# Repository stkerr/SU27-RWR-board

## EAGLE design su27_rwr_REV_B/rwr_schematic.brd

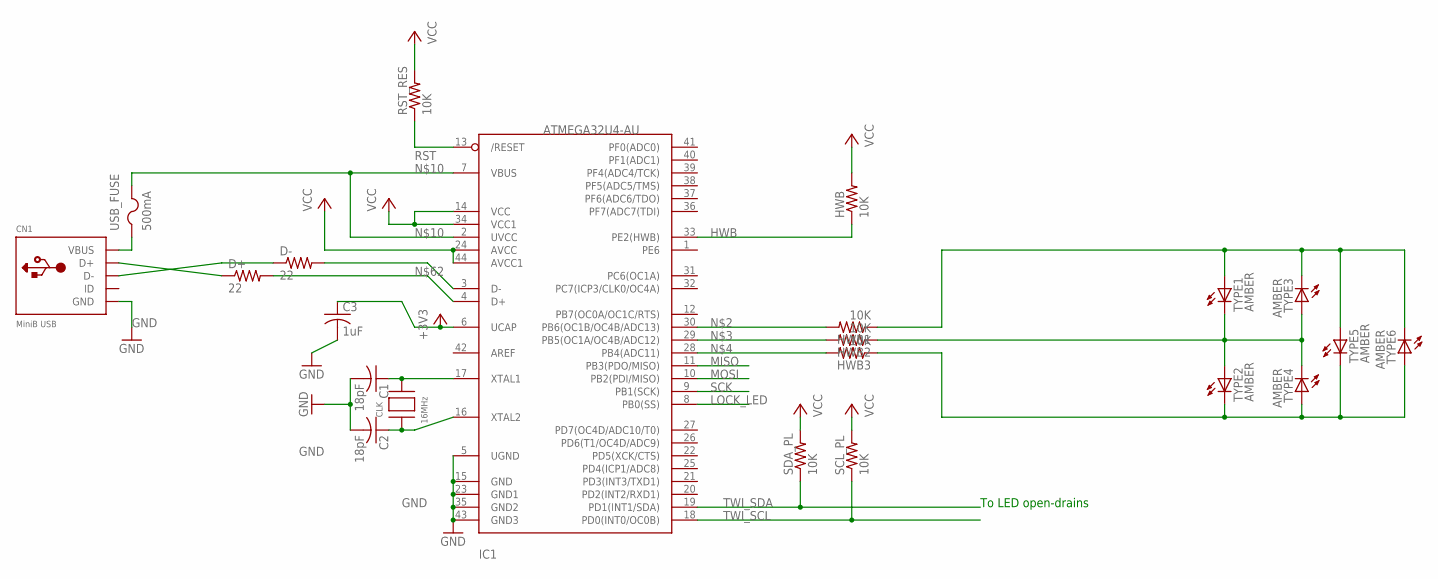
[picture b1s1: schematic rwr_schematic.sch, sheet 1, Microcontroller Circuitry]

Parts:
C1, C2: 18pF; C0805K
C3: 1uF; C0805K
CLK: 16MHz; NX5032
CN1: MiniB USB; USB-MINIB
D+: 22; R0805
D-: 22; R0805
HWB, HWB1, HWB2, HWB3: 10K; R0805
IC1: ATMEGA32U4-AU; TQFP44
RST_RES: 10K; R0805
SCL_PL: 10K; R0805
SDA_PL: 10K; R0805
TYPE1, TYPE2, TYPE3, TYPE4, TYPE5, TYPE6: AMBER; LED3MM
USB_FUSE: 500mA; R1206

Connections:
+3V3: C3.1, IC1.6 (UCAP)
GND: C1.2, C2.2, C3.2, CN1.GND, IC1.5 (UGND), IC1.15 (GND), IC1.23 (GND1), IC1.35 (GND2), IC1.43 (GND3); also elsewhere on the board
HWB: HWB.1, IC1.33 (PE2(HWB))
LOCK_LED: IC1.8 (PB0(SS)); also elsewhere on the board
MISO: IC1.11 (PB3(PDO/MISO)); also elsewhere on the board
MOSI: IC1.10 (PB2(PDI/MISO)); also elsewhere on the board
unnamed: HWB1.2, IC1.30 (PB6(OC1B/OC4B/ADC13))
unnamed: HWB2.2, IC1.29 (PB5(OC1A/OC4B/ADC12))
unnamed: HWB3.2, IC1.28 (PB4(ADC11))
unnamed: IC1.2 (UVCC), IC1.7 (VBUS), USB_FUSE.2
unnamed: D-.2, IC1.3 (D-)
unnamed: D+.2, IC1.4 (D+)
unnamed: C2.1, CLK.P$1, IC1.16 (XTAL2)
unnamed: C1.1, CLK.P$2, IC1.17 (XTAL1)
unnamed: CN1.D+, D+.1
unnamed: CN1.D-, D-.1
RST: IC1.13 (/RESET), RST_RES.1; also elsewhere on the board
SCK: IC1.9 (PB1(SCK)); also elsewhere on the board
TWI_SCL: IC1.18 (PD0(INT0/OC0B)), SCL_PL.1; also elsewhere on the board
TWI_SDA: IC1.19 (PD1(INT1/SDA)), SDA_PL.1; also elsewhere on the board
TYPE_LED0: HWB3.1, TYPE2.K (C), TYPE4.A, TYPE5.K (C), TYPE6.A
TYPE_LED1: HWB2.1, TYPE1.K (C), TYPE2.A, TYPE3.A, TYPE4.K (C)
TYPE_LED2: HWB1.1, TYPE1.A, TYPE3.K (C), TYPE5.A, TYPE6.K (C)
VBUS: CN1.VBUS, USB_FUSE.1
VCC: HWB.2, IC1.14 (VCC), IC1.24 (AVCC), IC1.34 (VCC1), IC1.44 (AVCC1), RST_RES.2, SCL_PL.2, SDA_PL.2; also elsewhere on the board

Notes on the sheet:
To LED open-drains

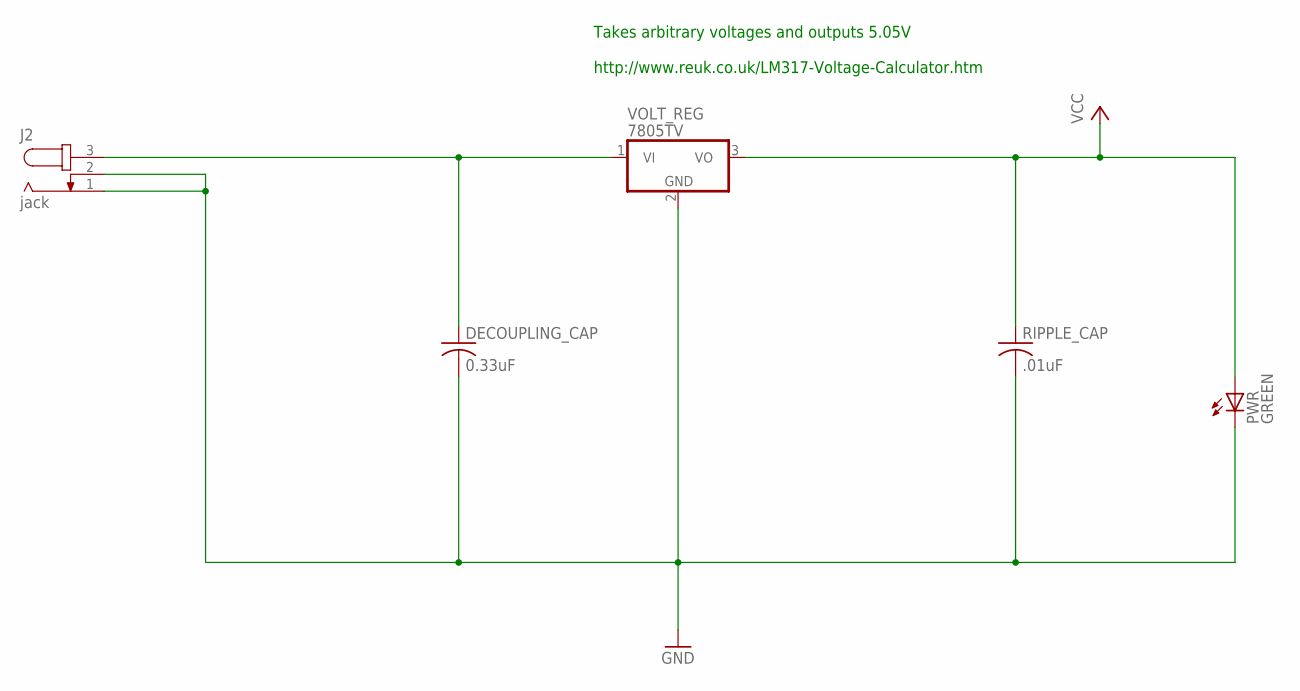
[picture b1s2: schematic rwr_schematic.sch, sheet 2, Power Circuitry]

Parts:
DECOUPLING_CAP: 0.33uF; C0805K
J2: jack; SPC4077
PWR: GREEN; CHIPLED_0805
RIPPLE_CAP: .01uF; C0805K
VOLT_REG: 7805TV; TO220V

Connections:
GND: DECOUPLING_CAP.2, J2.1, J2.2, PWR.C, RIPPLE_CAP.2, VOLT_REG.2 (GND); also elsewhere on the board
JACK_VCC: DECOUPLING_CAP.1, J2.3, VOLT_REG.1 (VI)
VCC: PWR.A, RIPPLE_CAP.1, VOLT_REG.3 (VO); also elsewhere on the board

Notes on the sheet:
Takes arbitrary voltages and outputs 5.05V http://www.reuk.co.uk/LM317-Voltage-Calculator.htm

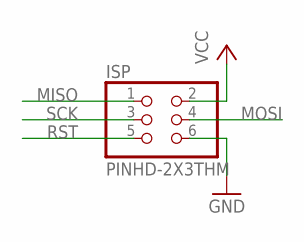
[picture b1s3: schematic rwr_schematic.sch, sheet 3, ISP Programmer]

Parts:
ISP: PINHD-2X3THM; ISP6

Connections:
GND: ISP.6; also elsewhere on the board
MISO: ISP.1; also elsewhere on the board
MOSI: ISP.4; also elsewhere on the board
RST: ISP.5; also elsewhere on the board
SCK: ISP.3; also elsewhere on the board
VCC: ISP.2; also elsewhere on the board

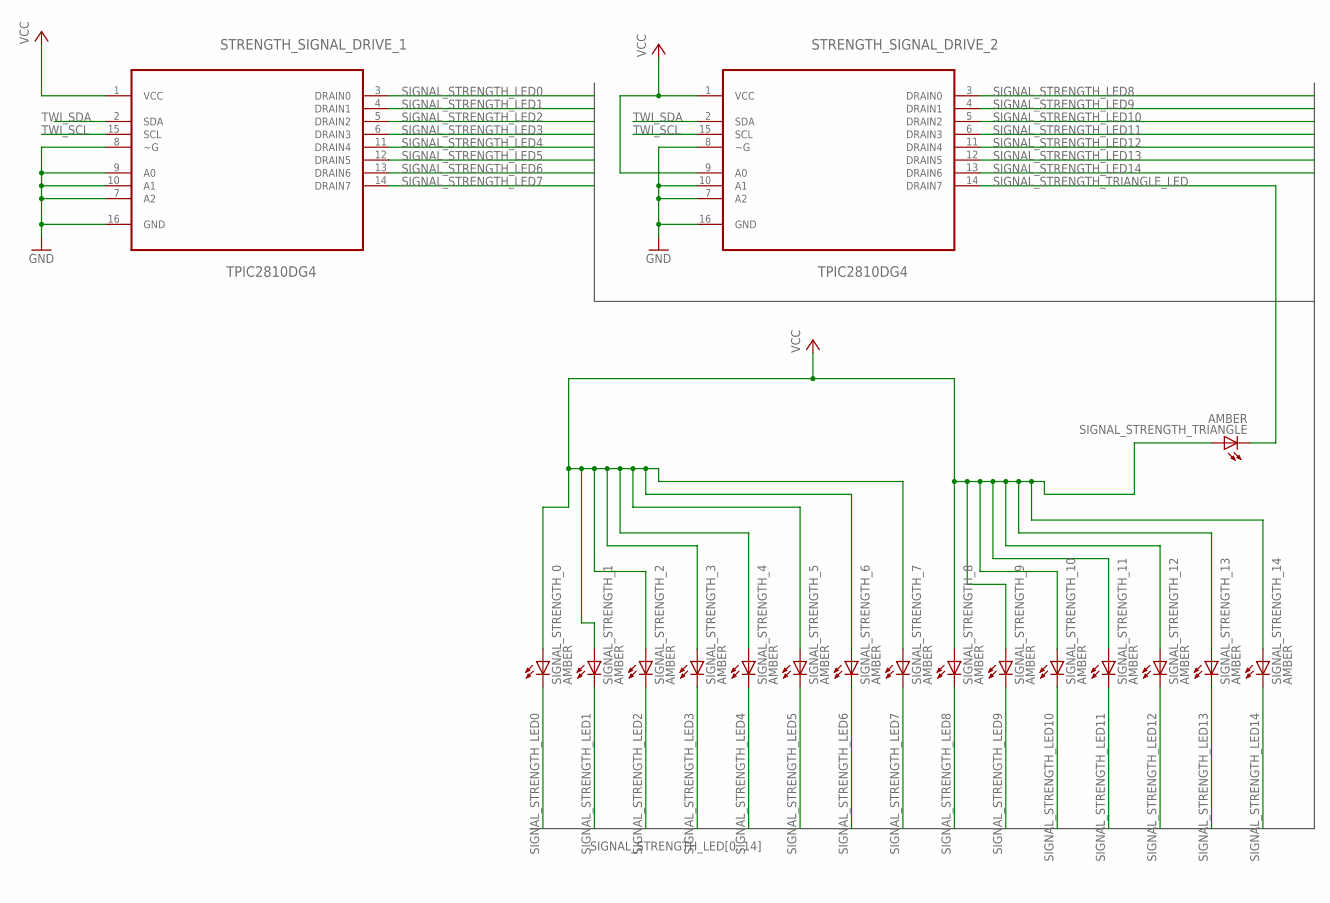
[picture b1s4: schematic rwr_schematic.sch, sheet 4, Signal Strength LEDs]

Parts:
SIGNAL_STRENGTH_0, SIGNAL_STRENGTH_1, SIGNAL_STRENGTH_2, SIGNAL_STRENGTH_3, SIGNAL_STRENGTH_4, SIGNAL_STRENGTH_5, SIGNAL_STRENGTH_6, SIGNAL_STRENGTH_7, SIGNAL_STRENGTH_8, SIGNAL_STRENGTH_9, SIGNAL_STRENGTH_10, SIGNAL_STRENGTH_11, SIGNAL_STRENGTH_12, SIGNAL_STRENGTH_13, SIGNAL_STRENGTH_14: AMBER; LED3MM
SIGNAL_STRENGTH_TRIANGLE: AMBER; LED3MM
STRENGTH_SIGNAL_DRIVE_1, STRENGTH_SIGNAL_DRIVE_2: TPIC2810DG4; SOIC127P600X175-16N

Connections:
GND: STRENGTH_SIGNAL_DRIVE_1.7 (A2), STRENGTH_SIGNAL_DRIVE_1.8 (~G), STRENGTH_SIGNAL_DRIVE_1.9 (A0), STRENGTH_SIGNAL_DRIVE_1.10 (A1), STRENGTH_SIGNAL_DRIVE_1.16 (GND), STRENGTH_SIGNAL_DRIVE_2.7 (A2), STRENGTH_SIGNAL_DRIVE_2.8 (~G), STRENGTH_SIGNAL_DRIVE_2.10 (A1), STRENGTH_SIGNAL_DRIVE_2.16 (GND); also elsewhere on the board
SIGNAL_STRENGTH_LED0: SIGNAL_STRENGTH_0.K (C), STRENGTH_SIGNAL_DRIVE_1.3 (DRAIN0)
SIGNAL_STRENGTH_LED1: SIGNAL_STRENGTH_1.K (C), STRENGTH_SIGNAL_DRIVE_1.4 (DRAIN1)
SIGNAL_STRENGTH_LED2: SIGNAL_STRENGTH_2.K (C), STRENGTH_SIGNAL_DRIVE_1.5 (DRAIN2)
SIGNAL_STRENGTH_LED3: SIGNAL_STRENGTH_3.K (C), STRENGTH_SIGNAL_DRIVE_1.6 (DRAIN3)
SIGNAL_STRENGTH_LED4: SIGNAL_STRENGTH_4.K (C), STRENGTH_SIGNAL_DRIVE_1.11 (DRAIN4)
SIGNAL_STRENGTH_LED5: SIGNAL_STRENGTH_5.K (C), STRENGTH_SIGNAL_DRIVE_1.12 (DRAIN5)
SIGNAL_STRENGTH_LED6: SIGNAL_STRENGTH_6.K (C), STRENGTH_SIGNAL_DRIVE_1.13 (DRAIN6)
SIGNAL_STRENGTH_LED7: SIGNAL_STRENGTH_7.K (C), STRENGTH_SIGNAL_DRIVE_1.14 (DRAIN7)
SIGNAL_STRENGTH_LED8: SIGNAL_STRENGTH_8.K (C), STRENGTH_SIGNAL_DRIVE_2.3 (DRAIN0)
SIGNAL_STRENGTH_LED9: SIGNAL_STRENGTH_9.K (C), STRENGTH_SIGNAL_DRIVE_2.4 (DRAIN1)
SIGNAL_STRENGTH_LED10: SIGNAL_STRENGTH_10.K (C), STRENGTH_SIGNAL_DRIVE_2.5 (DRAIN2)
SIGNAL_STRENGTH_LED11: SIGNAL_STRENGTH_11.K (C), STRENGTH_SIGNAL_DRIVE_2.6 (DRAIN3)
SIGNAL_STRENGTH_LED12: SIGNAL_STRENGTH_12.K (C), STRENGTH_SIGNAL_DRIVE_2.11 (DRAIN4)
SIGNAL_STRENGTH_LED13: SIGNAL_STRENGTH_13.K (C), STRENGTH_SIGNAL_DRIVE_2.12 (DRAIN5)
SIGNAL_STRENGTH_LED14: SIGNAL_STRENGTH_14.K (C), STRENGTH_SIGNAL_DRIVE_2.13 (DRAIN6)
SIGNAL_STRENGTH_TRIANGLE_LED: SIGNAL_STRENGTH_TRIANGLE.K (C), STRENGTH_SIGNAL_DRIVE_2.14 (DRAIN7)
TWI_SCL: STRENGTH_SIGNAL_DRIVE_1.15 (SCL), STRENGTH_SIGNAL_DRIVE_2.15 (SCL); also elsewhere on the board
TWI_SDA: STRENGTH_SIGNAL_DRIVE_1.2 (SDA), STRENGTH_SIGNAL_DRIVE_2.2 (SDA); also elsewhere on the board
VCC: SIGNAL_STRENGTH_0.A, SIGNAL_STRENGTH_1.A, SIGNAL_STRENGTH_2.A, SIGNAL_STRENGTH_3.A, SIGNAL_STRENGTH_4.A, SIGNAL_STRENGTH_5.A, SIGNAL_STRENGTH_6.A, SIGNAL_STRENGTH_7.A, SIGNAL_STRENGTH_8.A, SIGNAL_STRENGTH_9.A, SIGNAL_STRENGTH_10.A, SIGNAL_STRENGTH_11.A, SIGNAL_STRENGTH_12.A, SIGNAL_STRENGTH_13.A, SIGNAL_STRENGTH_14.A, SIGNAL_STRENGTH_TRIANGLE.A, STRENGTH_SIGNAL_DRIVE_1.1 (VCC), STRENGTH_SIGNAL_DRIVE_2.1 (VCC), STRENGTH_SIGNAL_DRIVE_2.9 (A0); also elsewhere on the board

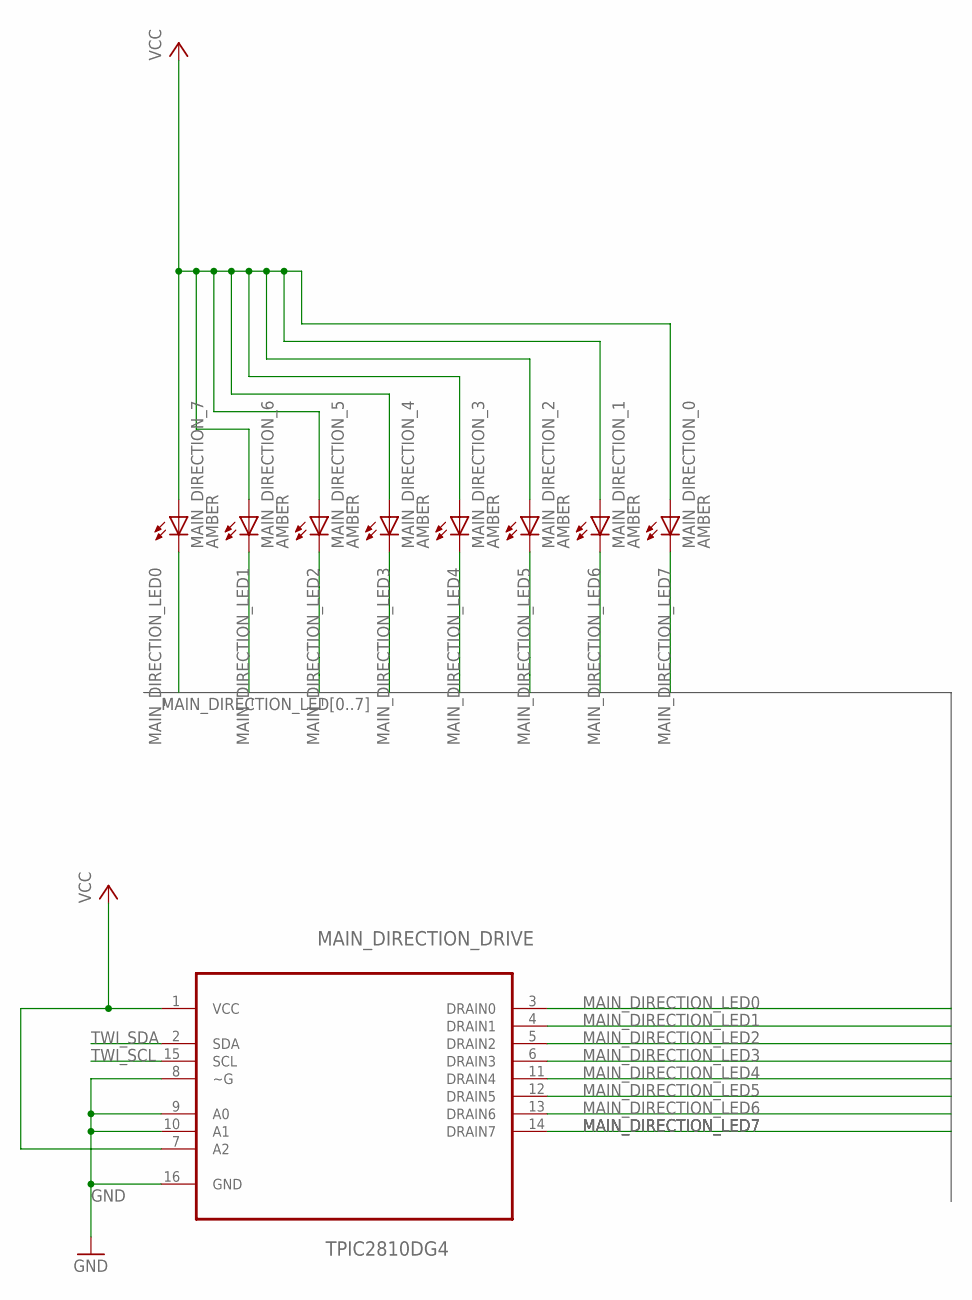
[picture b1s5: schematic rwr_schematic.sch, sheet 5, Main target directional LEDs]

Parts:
MAIN_DIRECTION_0, MAIN_DIRECTION_1, MAIN_DIRECTION_2, MAIN_DIRECTION_3, MAIN_DIRECTION_4, MAIN_DIRECTION_5, MAIN_DIRECTION_6, MAIN_DIRECTION_7: AMBER; LED3MM
MAIN_DIRECTION_DRIVE: TPIC2810DG4; SOIC127P600X175-16N

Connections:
GND: MAIN_DIRECTION_DRIVE.8 (~G), MAIN_DIRECTION_DRIVE.9 (A0), MAIN_DIRECTION_DRIVE.10 (A1), MAIN_DIRECTION_DRIVE.16 (GND); also elsewhere on the board
MAIN_DIRECTION_LED0: MAIN_DIRECTION_7.K (C), MAIN_DIRECTION_DRIVE.3 (DRAIN0)
MAIN_DIRECTION_LED1: MAIN_DIRECTION_6.K (C), MAIN_DIRECTION_DRIVE.4 (DRAIN1)
MAIN_DIRECTION_LED2: MAIN_DIRECTION_5.K (C), MAIN_DIRECTION_DRIVE.5 (DRAIN2)
MAIN_DIRECTION_LED3: MAIN_DIRECTION_4.K (C), MAIN_DIRECTION_DRIVE.6 (DRAIN3)
MAIN_DIRECTION_LED4: MAIN_DIRECTION_3.K (C), MAIN_DIRECTION_DRIVE.11 (DRAIN4)
MAIN_DIRECTION_LED5: MAIN_DIRECTION_2.K (C), MAIN_DIRECTION_DRIVE.12 (DRAIN5)
MAIN_DIRECTION_LED6: MAIN_DIRECTION_1.K (C), MAIN_DIRECTION_DRIVE.13 (DRAIN6)
MAIN_DIRECTION_LED7: MAIN_DIRECTION_0.K (C), MAIN_DIRECTION_DRIVE.14 (DRAIN7)
TWI_SCL: MAIN_DIRECTION_DRIVE.15 (SCL); also elsewhere on the board
TWI_SDA: MAIN_DIRECTION_DRIVE.2 (SDA); also elsewhere on the board
VCC: MAIN_DIRECTION_0.A, MAIN_DIRECTION_1.A, MAIN_DIRECTION_2.A, MAIN_DIRECTION_3.A, MAIN_DIRECTION_4.A, MAIN_DIRECTION_5.A, MAIN_DIRECTION_6.A, MAIN_DIRECTION_7.A, MAIN_DIRECTION_DRIVE.1 (VCC), MAIN_DIRECTION_DRIVE.7 (A2); also elsewhere on the board

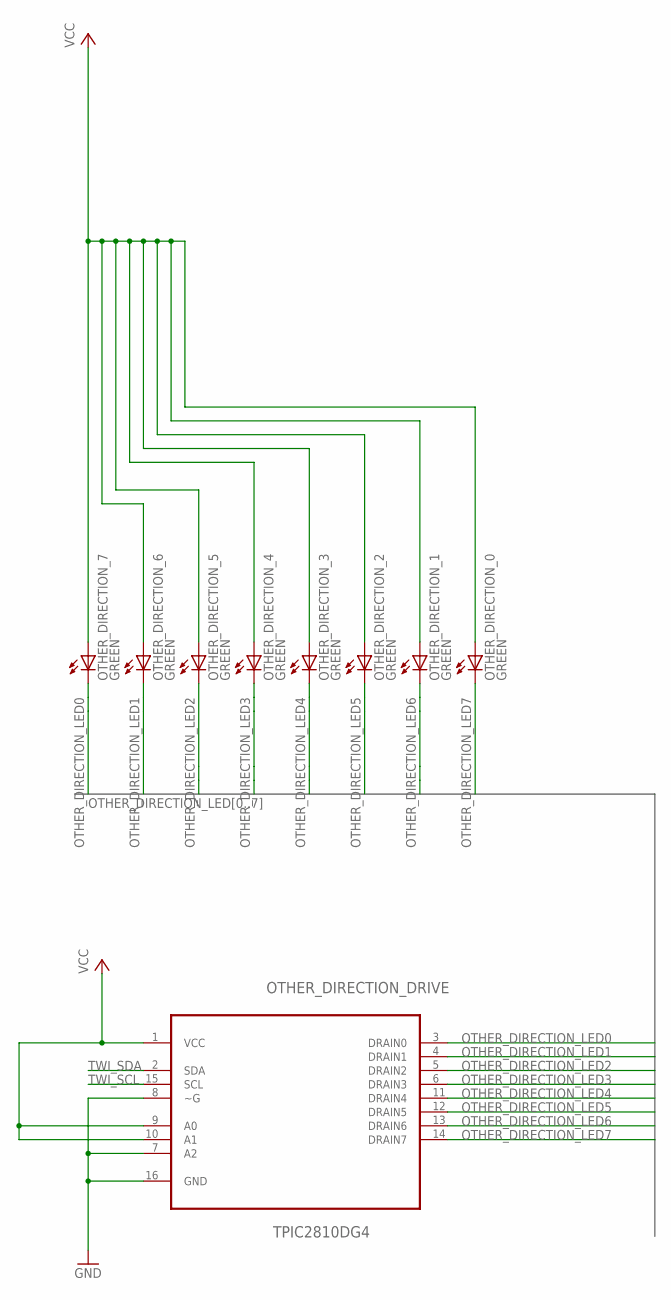
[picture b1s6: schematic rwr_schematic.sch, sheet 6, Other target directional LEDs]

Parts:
OTHER_DIRECTION_0, OTHER_DIRECTION_1, OTHER_DIRECTION_2, OTHER_DIRECTION_3, OTHER_DIRECTION_4, OTHER_DIRECTION_5, OTHER_DIRECTION_6, OTHER_DIRECTION_7: GREEN; LED3MM
OTHER_DIRECTION_DRIVE: TPIC2810DG4; SOIC127P600X175-16N

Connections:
GND: OTHER_DIRECTION_DRIVE.7 (A2), OTHER_DIRECTION_DRIVE.8 (~G), OTHER_DIRECTION_DRIVE.16 (GND); also elsewhere on the board
OTHER_DIRECTION_LED0: OTHER_DIRECTION_7.K (C), OTHER_DIRECTION_DRIVE.3 (DRAIN0)
OTHER_DIRECTION_LED1: OTHER_DIRECTION_6.K (C), OTHER_DIRECTION_DRIVE.4 (DRAIN1)
OTHER_DIRECTION_LED2: OTHER_DIRECTION_5.K (C), OTHER_DIRECTION_DRIVE.5 (DRAIN2)
OTHER_DIRECTION_LED3: OTHER_DIRECTION_4.K (C), OTHER_DIRECTION_DRIVE.6 (DRAIN3)
OTHER_DIRECTION_LED4: OTHER_DIRECTION_3.K (C), OTHER_DIRECTION_DRIVE.11 (DRAIN4)
OTHER_DIRECTION_LED5: OTHER_DIRECTION_2.K (C), OTHER_DIRECTION_DRIVE.12 (DRAIN5)
OTHER_DIRECTION_LED6: OTHER_DIRECTION_1.K (C), OTHER_DIRECTION_DRIVE.13 (DRAIN6)
OTHER_DIRECTION_LED7: OTHER_DIRECTION_0.K (C), OTHER_DIRECTION_DRIVE.14 (DRAIN7)
TWI_SCL: OTHER_DIRECTION_DRIVE.15 (SCL); also elsewhere on the board
TWI_SDA: OTHER_DIRECTION_DRIVE.2 (SDA); also elsewhere on the board
VCC: OTHER_DIRECTION_0.A, OTHER_DIRECTION_1.A, OTHER_DIRECTION_2.A, OTHER_DIRECTION_3.A, OTHER_DIRECTION_4.A, OTHER_DIRECTION_5.A, OTHER_DIRECTION_6.A, OTHER_DIRECTION_7.A, OTHER_DIRECTION_DRIVE.1 (VCC), OTHER_DIRECTION_DRIVE.9 (A0), OTHER_DIRECTION_DRIVE.10 (A1); also elsewhere on the board

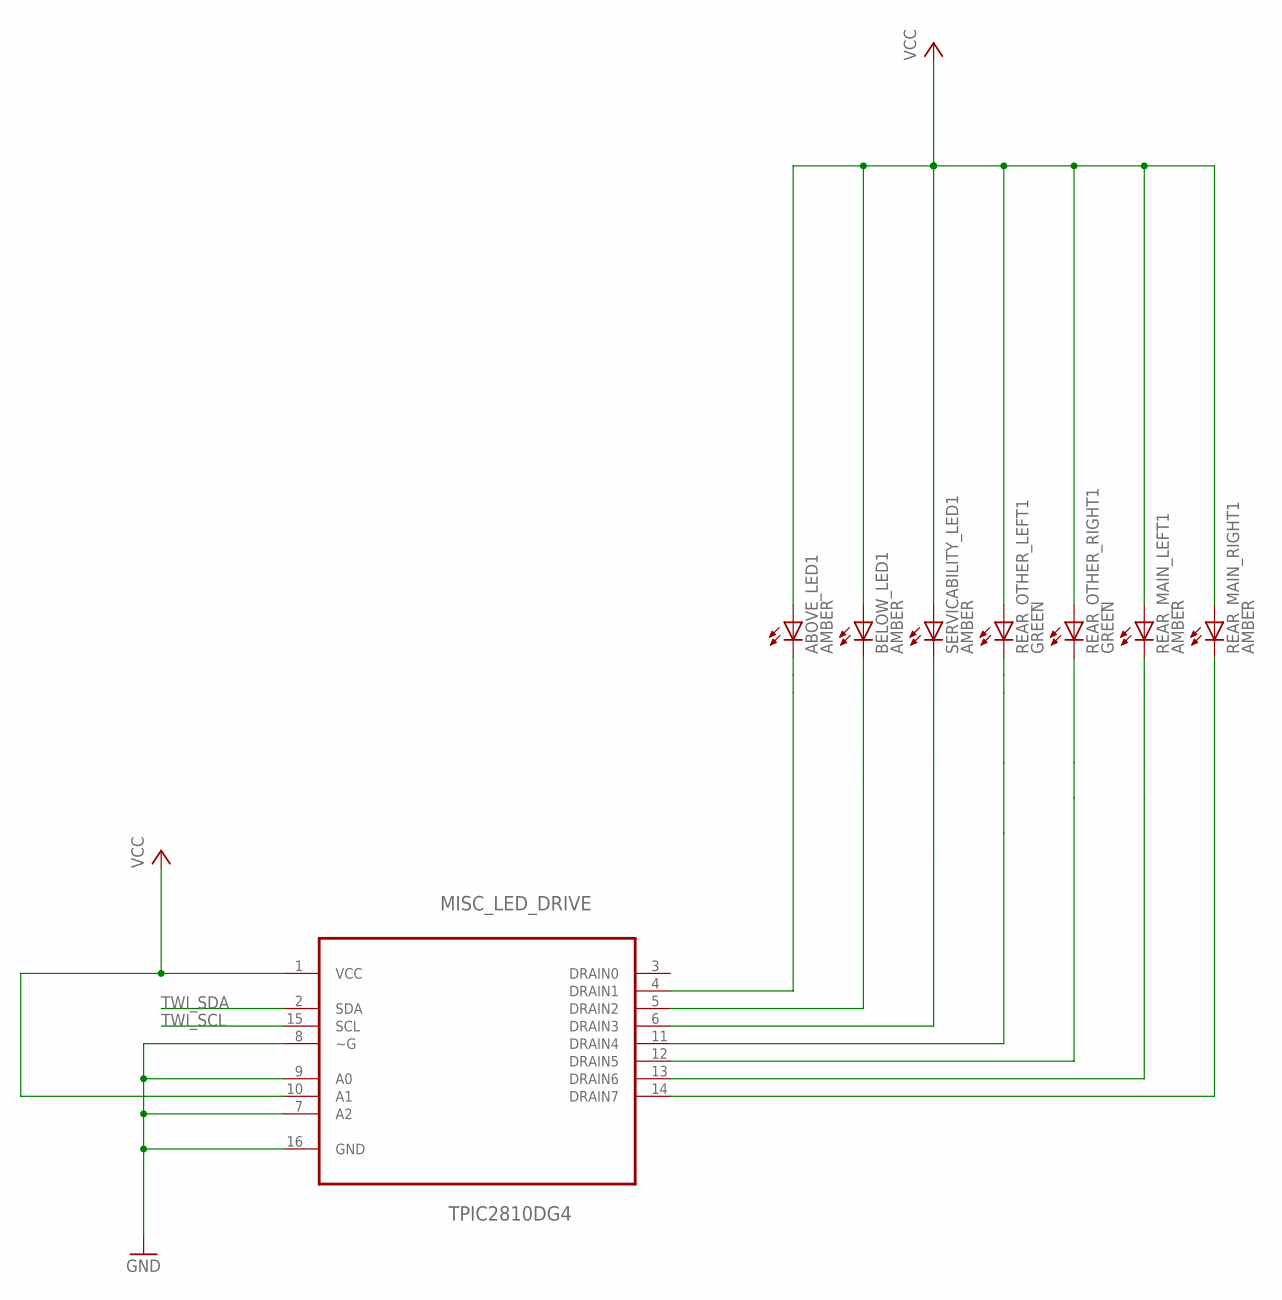
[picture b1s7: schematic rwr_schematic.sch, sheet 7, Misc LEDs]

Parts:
ABOVE_LED1: AMBER; LED3MM
BELOW_LED1: AMBER; LED3MM
MISC_LED_DRIVE: TPIC2810DG4; SOIC127P600X175-16N
REAR_MAIN_LEFT1: AMBER; LED3MM
REAR_MAIN_RIGHT1: AMBER; LED3MM
REAR_OTHER_LEFT1: GREEN; LED3MM
REAR_OTHER_RIGHT1: GREEN; LED3MM
SERVICABILITY_LED1: AMBER; LED3MM

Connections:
GND: MISC_LED_DRIVE.7 (A2), MISC_LED_DRIVE.8 (~G), MISC_LED_DRIVE.9 (A0), MISC_LED_DRIVE.16 (GND); also elsewhere on the board
unnamed: MISC_LED_DRIVE.12 (DRAIN5), REAR_OTHER_RIGHT1.K (C)
unnamed: MISC_LED_DRIVE.14 (DRAIN7), REAR_MAIN_RIGHT1.K (C)
unnamed: ABOVE_LED1.K (C), MISC_LED_DRIVE.4 (DRAIN1)
unnamed: MISC_LED_DRIVE.6 (DRAIN3), SERVICABILITY_LED1.K (C)
unnamed: MISC_LED_DRIVE.11 (DRAIN4), REAR_OTHER_LEFT1.K (C)
unnamed: BELOW_LED1.K (C), MISC_LED_DRIVE.5 (DRAIN2)
REAR_MAIN_LEFT1: MISC_LED_DRIVE.13 (DRAIN6), REAR_MAIN_LEFT1.K (C)
TWI_SCL: MISC_LED_DRIVE.15 (SCL); also elsewhere on the board
TWI_SDA: MISC_LED_DRIVE.2 (SDA); also elsewhere on the board
VCC: ABOVE_LED1.A, BELOW_LED1.A, MISC_LED_DRIVE.1 (VCC), MISC_LED_DRIVE.10 (A1), REAR_MAIN_LEFT1.A, REAR_MAIN_RIGHT1.A, REAR_OTHER_LEFT1.A, REAR_OTHER_RIGHT1.A, SERVICABILITY_LED1.A; also elsewhere on the board

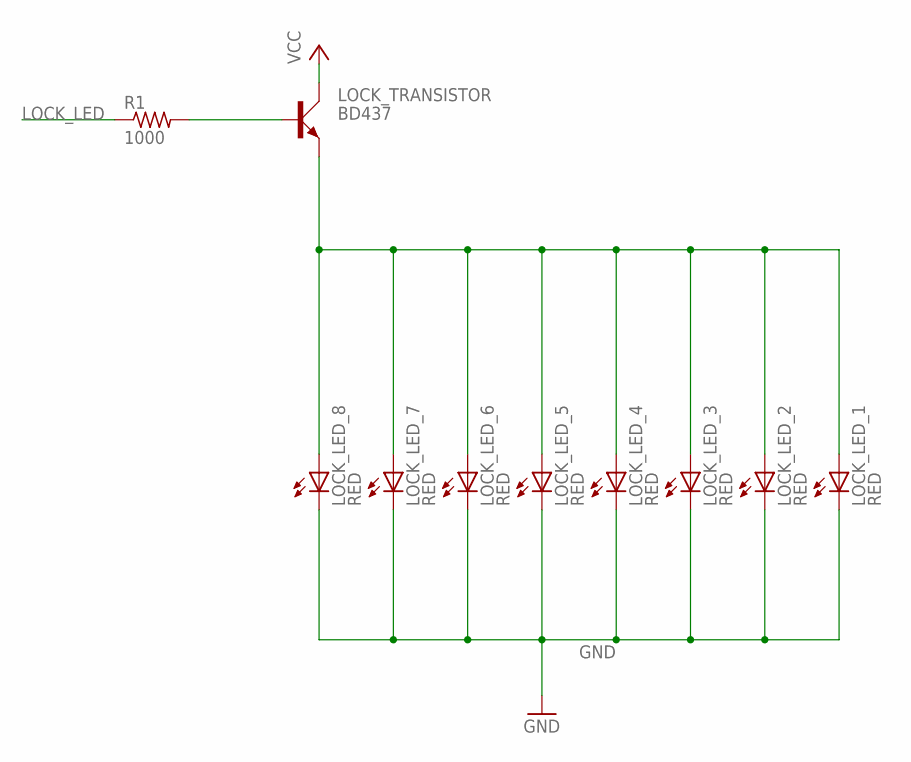
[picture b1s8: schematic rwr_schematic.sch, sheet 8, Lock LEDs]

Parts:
LOCK_LED_1, LOCK_LED_2, LOCK_LED_3, LOCK_LED_4, LOCK_LED_5, LOCK_LED_6, LOCK_LED_7, LOCK_LED_8: RED; LED3MM
LOCK_TRANSISTOR: BD437; TO126AV
R1: 1000; R0805

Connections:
GND: LOCK_LED_1.K (C), LOCK_LED_2.K (C), LOCK_LED_3.K (C), LOCK_LED_4.K (C), LOCK_LED_5.K (C), LOCK_LED_6.K (C), LOCK_LED_7.K (C), LOCK_LED_8.K (C); also elsewhere on the board
LOCK_LED: R1.1; also elsewhere on the board
LOCK_LED_1: LOCK_LED_1.A, LOCK_LED_2.A, LOCK_LED_3.A, LOCK_LED_4.A, LOCK_LED_5.A, LOCK_LED_6.A, LOCK_LED_7.A, LOCK_LED_8.A, LOCK_TRANSISTOR.E
unnamed: LOCK_TRANSISTOR.B, R1.2
VCC: LOCK_TRANSISTOR.C; also elsewhere on the board

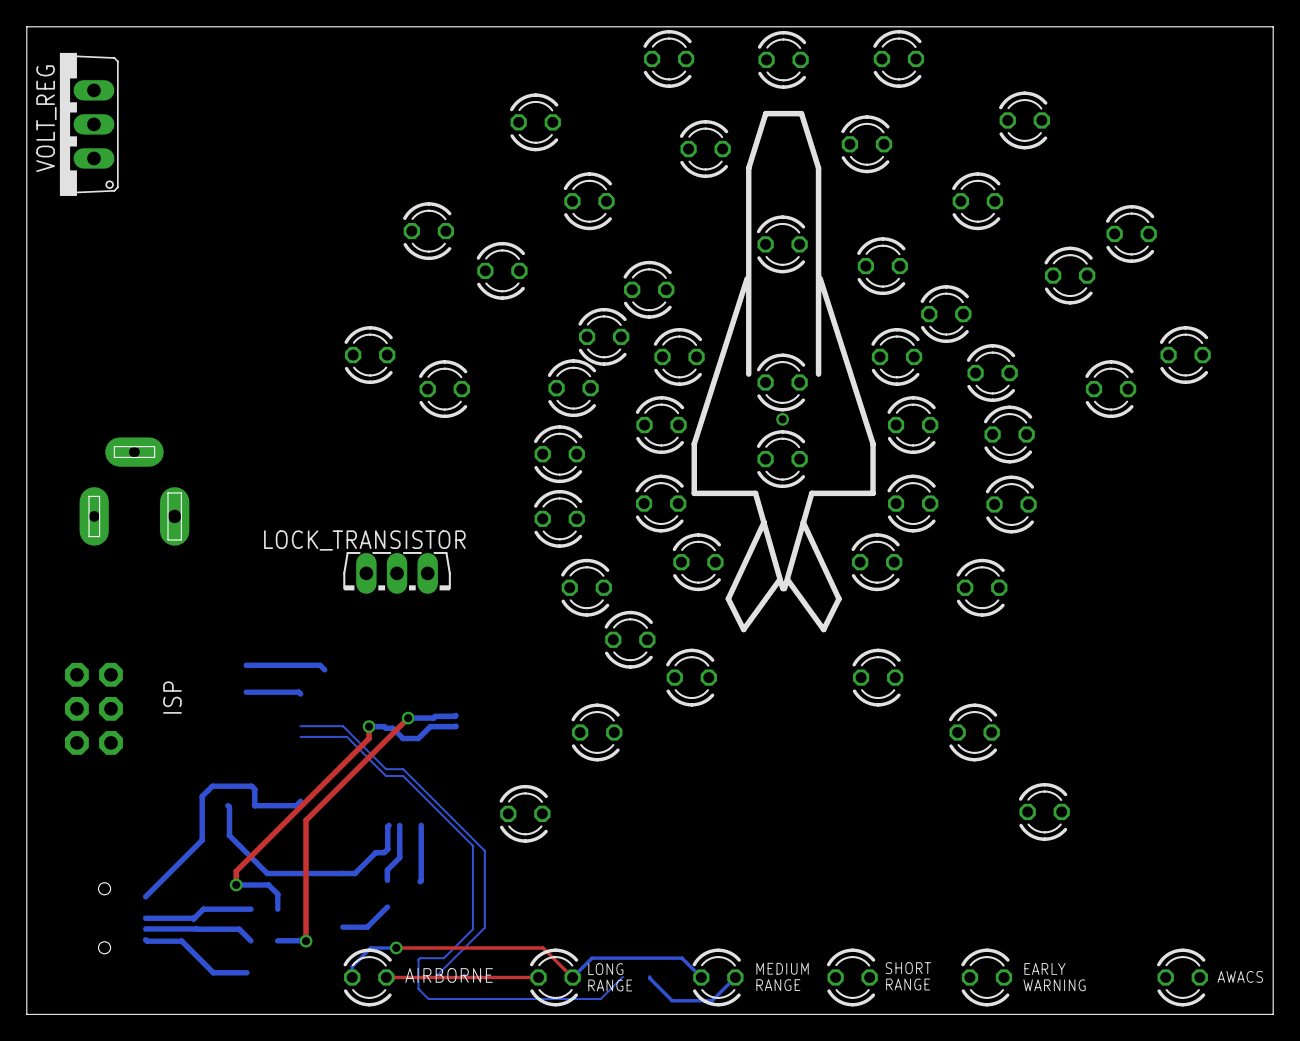
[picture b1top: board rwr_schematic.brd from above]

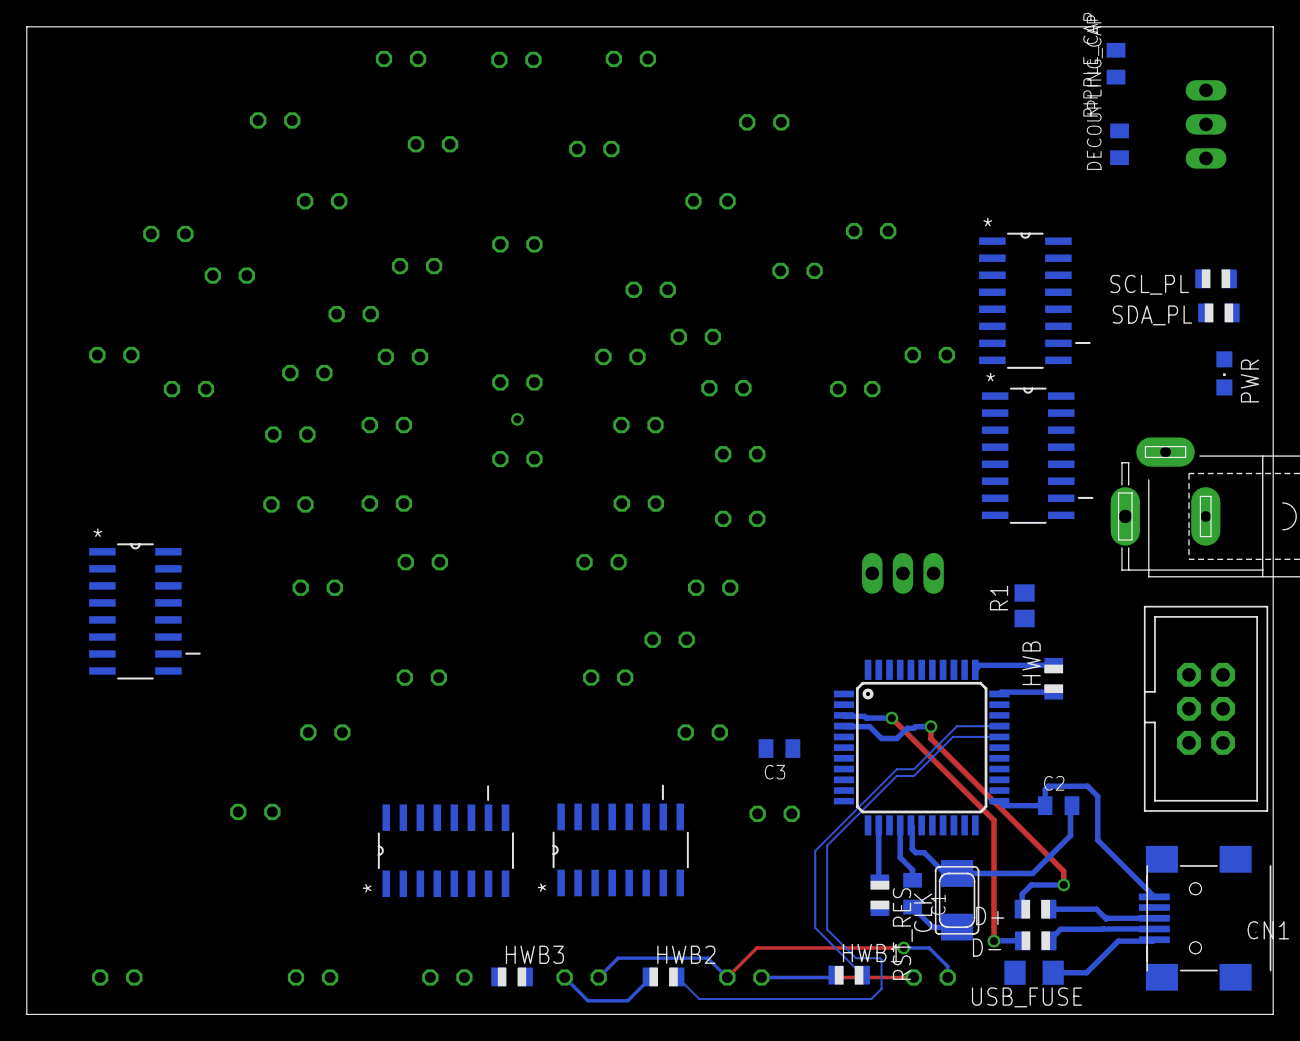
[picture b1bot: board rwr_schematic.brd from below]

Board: 2 copper layers, 93.0 x 73.7 mm, 82 parts (27 on the bottom side), 67 nets.

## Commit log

2021-08-19 Initial commit of 3 revs. Rev A is the first that was built
